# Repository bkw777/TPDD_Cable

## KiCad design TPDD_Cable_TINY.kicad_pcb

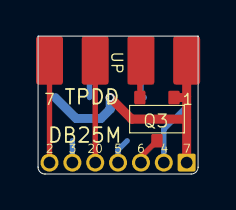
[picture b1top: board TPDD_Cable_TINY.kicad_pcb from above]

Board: 2 copper layers, 8.9 x 7.7 mm, 5 parts (0 on the bottom side), 10 nets.

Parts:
J1: Conn_01x07; 1x7x2mm
J2: TPDD; 2-6-2_tpdd
Q1, Q2, Q3: DTA114E; SC-59

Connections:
/CTS_232: J1.4, Q2.3
/CTS_TTL: J2.4, Q2.2
/DSR_232: J1.3, Q3.3
/DSR_TTL: J2.3, Q3.2
/DTR: J1.5, J2.5
/RTS: J1.2, J2.2
/RX_232: J1.6, Q1.3
/RX_TTL: J2.6, Q1.2
/TX: J1.7, J2.7
GNDS: J1.1, J2.1, Q1.1, Q2.1, Q3.1

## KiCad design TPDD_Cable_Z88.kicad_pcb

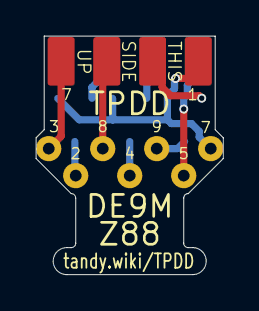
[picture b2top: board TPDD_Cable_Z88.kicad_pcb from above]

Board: 2 copper layers, 10.4 x 13.2 mm, 5 parts (0 on the bottom side), 10 nets.

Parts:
J1: Wire Solder Pads; D7_1.5mm_wirepads
J2: TPDD; 2-6-2_tpdd
Q1, Q2, Q3: DTA114EKA; SC-59

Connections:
/CTS: J1.4, Q2.3
/CTS_TTL: J2.4, Q2.2
/DSR: J1.5, Q1.3
/DSR_TTL: J2.3, Q1.2
/DTR: J1.3, J2.5
/RTS: J1.6, J2.2
/RX: J1.2, Q3.3
/RX_TTL: J2.6, Q3.2
/SG: J1.7, J2.1, Q1.1, Q2.1, Q3.1
/TX: J1.1, J2.7

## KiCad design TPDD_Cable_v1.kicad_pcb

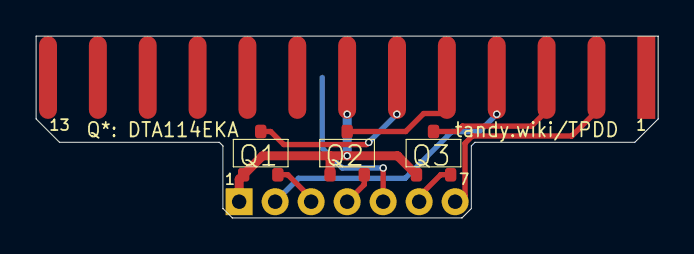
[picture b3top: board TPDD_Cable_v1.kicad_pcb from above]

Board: 2 copper layers, 34.6 x 10.1 mm, 5 parts (0 on the bottom side), 10 nets.

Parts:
J1: 7 x wire pads; pins_1x7_2mm
J2: DB25_Male; DSUB-25_Male_EdgeMount_P2.77mm
Q1, Q2, Q3: DTA114EKA; SC-59

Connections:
/CTS: J2.5, Q2.3
/CTS_TTL: J1.4, Q2.2
/DSR: J2.6, Q1.3
/DSR_TTL: J1.3, Q1.2
/DTR: J1.5, J2.20
/GND: J1.1, J2.7, Q1.1, Q2.1, Q3.1
/RTS: J1.2, J2.4
/RXD: J2.3, Q3.3
/RXD_TTL: J1.6, Q3.2
/TXD: J1.7, J2.2
